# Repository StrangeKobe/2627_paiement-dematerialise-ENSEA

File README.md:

# Plateforme de paiement dématérialisé ENSEA

> Reprise et finalisation d'un système de paiement cashless destiné aux
> associations de l'ENSEA.

**Statut :** reprise du projet / développement en cours\
**Cadre :** projet étudiant ENSEA 2026--2027

------------------------------------------------------------------------

## 1. Présentation

Le projet vise à mettre en place une plateforme de paiement
dématérialisé pour les associations de l'ENSEA.

Le principe est de permettre à un étudiant de disposer d'un
**portefeuille prépayé**, puis d'utiliser ce solde pour effectuer des
achats auprès des associations de l'école.

L'identification prévue repose sur :

-   un **QR code dynamique** ;
-   à terme, la **carte étudiante RFID**.

Le système doit réunir :

-   une application web ;
-   une caisse ;
-   un terminal de paiement portable ;
-   une base de données ;
-   un système de recharge ;
-   des fonctions de suivi des ventes et des soldes.

Le projet est une **reprise d'un travail existant**. Une partie
importante du logiciel et du matériel existe déjà, mais doit être
vérifiée avant d'être considérée comme fonctionnelle.

> **Principe de reprise :** une fonctionnalité annoncée comme réalisée
> doit être testée et classée comme `conforme`, `défaillante` ou
> `non testable`.

------------------------------------------------------------------------

## 2. Objectifs de la V2

L'objectif de la V2 est de disposer d'un ensemble cohérent et
démontrable comprenant :

1.  une application de paiement fonctionnelle ;
2.  une caisse corrigée et testée ;
3.  un terminal de paiement corrigé et testé ;
4.  une identification par QR code et, si possible dans le périmètre
    retenu, par RFID ;
5.  une recharge en ligne réellement intégrée ;
6.  une gestion fiable des soldes et des transactions ;
7.  une documentation permettant la reprise du projet.

Le planning de travail proposé dans le précadrage est de **10
semaines**, à confirmer avec les encadrants.

------------------------------------------------------------------------

## 3. État actuel

### 3.1 Logiciel

  Élément                 État actuel
  ----------------------- -----------------------------------------------------
  Backend                 Django
  Base de développement   SQLite
  Interface               Templates Django + Bootstrap
  QR code                 QR dynamique / caméra du navigateur
  Paiement en ligne       HelloAsso prévu, intégration réelle à terminer
  RFID                    Champ `uid_rfid` présent, lecture réelle à intégrer
  Exports                 Excel avec `openpyxl`
  Emails                  Reçus et codes selon la configuration

### 3.2 Fonctionnalités déclarées comme réalisées

Le projet initial déclare notamment :

-   portefeuille prépayé par étudiant ;
-   débit/crédit atomique ;
-   paiement par QR code dynamique ;
-   vente catalogue ;
-   vente à montant libre ;
-   gestion du catalogue et des stocks ;
-   adhésions ;
-   recharge en espèces ;
-   rôles et droits par pôle ;
-   codes de sécurité ;
-   espace administrateur école ;
-   exports Excel ;
-   reçus par email ;
-   anonymisation après suppression de compte.

**Ces fonctionnalités doivent être vérifiées pendant la phase de
diagnostic.**

### 3.3 Fonctionnalités restantes identifiées

-   intégration réelle de HelloAsso ;
-   lecture RFID ;
-   blocage réversible d'un compte ou d'un QR compromis ;
-   tarif adhérent / non-adhérent ;
-   authentification CAS de l'école ;
-   passage à PostgreSQL ;
-   préparation de la mise en production ;
-   finalisation des CGU ;
-   V2 des PCB ;
-   éventuellement tableau de bord statistique et notifications.

Le périmètre définitif sera validé après le diagnostic.

------------------------------------------------------------------------

## 4. Architecture générale

``` text
                    +--------------------+
                    |      Étudiant      |
                    | QR / carte RFID    |
                    +---------+----------+
                              |
                              v
                    +--------------------+
                    | Application Django |
                    +---------+----------+
                              |
             +----------------+----------------+
             |                |                |
             v                v                v
       +-----------+    +-----------+    +-------------+
       |   Caisse  |    |  Terminal |    |   Recharge  |
       | Raspberry |    |  portable |    |   en ligne  |
       +-----------+    +-----------+    +-------------+
                              |
                              v
                    +--------------------+
                    |   Base de données  |
                    | comptes / soldes / |
                    | ventes / adhésions |
                    +--------------------+
```

------------------------------------------------------------------------

## 5. Fonctionnement cible d'un paiement

``` text
1. L'étudiant présente son QR code ou sa carte
                ↓
2. Le vendeur identifie l'étudiant
                ↓
3. L'application vérifie les droits et le solde
                ↓
4. Le paiement est accepté ou refusé
                ↓
5. Le solde étudiant est débité
                ↓
6. La recette du pôle est enregistrée
                ↓
7. La transaction est conservée dans l'historique
```

Les mécanismes exacts doivent être confirmés par les tests de reprise.

------------------------------------------------------------------------

## 6. Rôles

Le modèle applicatif repose sur des affectations associant un
utilisateur, un pôle, un rôle et éventuellement des droits
supplémentaires.

  -----------------------------------------------------------------------
  Rôle                    Portée                  Fonction principale
  ----------------------- ----------------------- -----------------------
  **Admin école**         Globale                 Comptes, rôles, codes
                                                  de sécurité, recettes
                                                  agrégées

  **Admin ADE**           Globale                 Gestion des pôles et
                                                  opérations ADE

  **Admin de pôle**       Un pôle                 Catalogue, événements,
                                                  équipe, adhésions,
                                                  exports

  **Vendeur**             Un pôle                 Encaissement et ventes
  -----------------------------------------------------------------------

------------------------------------------------------------------------

## 7. Matériel

Le projet comprend deux équipements électroniques.

### 7.1 Caisse

Éléments principaux identifiés :

-   Raspberry Pi 5 ;
-   alimentation ;
-   conversion 12 V → 5 V ;
-   commande du tiroir-caisse ;
-   périphériques d'encaissement.

Le PCB V1 existe mais présente des défauts identifiés dans la
documentation matérielle.

**Travail V2 :**

-   audit du schéma ;
-   vérification des empreintes ;
-   correction des composants de puissance ;
-   vérification de l'alimentation ;
-   vérification du routage ;
-   génération d'une BOM à jour ;
-   fabrication ;
-   tests électriques ;
-   tests fonctionnels.

### 7.2 Terminal portable

Éléments principaux identifiés :

-   Raspberry Pi Zero 2 W ;
-   HAT UPS Geekworm X306 ;
-   batterie 18650 ;
-   RC522 ;
-   écran OLED SSD1327 ;
-   périphériques d'identification et de signalisation.

Le PCB V1 doit également être vérifié et corrigé avant une nouvelle
fabrication.

> Le lecteur QR actuellement disponible est identifié comme **à
> revoir**, notamment concernant son interface. Ne pas commander une
> nouvelle série de cartes ou de composants avant validation.

------------------------------------------------------------------------

## 8. Structure du dépôt

``` text
2026_Stage_Caisse_Ensea/
│
├── README.md
│
├── Documents/
│   ├── conformite_reglementaire/
│   ├── Systèmes de paiment/
│   └── Réunion/
│
├── Hardware/
│   ├── README.md
│   ├── PROBLEMES_MATERIEL.md
│   ├── PCB_Caisse_Enregistreuse/
│   └── PCB_Caisse_Dématérialisée/
│
├── Software/
│   ├── README.md
│   ├── Raspberry/
│   ├── Diagramme_BDD/
│   ├── Tutoriel_Application_Cashless_ENSEA/
│   ├── First_Test_Appli_Django/
│   └── Ancienne_réflexion/
│
└── Images/
```

### Documents importants

  Besoin                           Document / dossier
  -------------------------------- ---------------------------------------
  Comprendre l'application         `Software/README.md`
  Comprendre la base et les flux   `Software/Diagramme_BDD/`
  Installer les Raspberry Pi       `Software/Raspberry/`
  Reprendre les PCB                `Hardware/README.md`
  Problèmes matériels connus       `Hardware/PROBLEMES_MATERIEL.md`
  Réglementation                   `Documents/conformite_reglementaire/`
  Benchmark / prestataires         `Documents/Systèmes de paiment/`
  Historique                       `Documents/Réunion/`

Les dossiers `Software/First_Test_Appli_Django/` et
`Software/Ancienne_réflexion/` sont historiques et ne décrivent pas
nécessairement l'architecture actuelle.

------------------------------------------------------------------------

## 9. Plan de reprise
## Planning du projet

Le projet a débuté le **23 septembre 2026** et la livraison est prévue
début **mars 2027**.

Le planning est structuré selon les lots du WBS présentés dans le document
de précadrage.

```mermaid
gantt
    title Projet Paiement dématérialisé ENSEA V2
    dateFormat YYYY-MM-DD
    axisFormat %d/%m

    section W1 — Cadrage

    Cadrage du projet                 :w1_1, 2026-09-23, 10d
    Définition du périmètre V2       :w1_2, 2026-09-29, 12d
    Objectifs / contraintes / risques :w1_3, 2026-10-02, 10d
    Document de précadrage            :w1_4, 2026-10-05, 12d
    Jalon — Cadrage terminé          :milestone, w1_end, 2026-10-16, 0d

    section W2 — Diagnostic

    Reprise du dépôt                 :w2_1, 2026-09-23, 15d
    Audit logiciel                   :w2_2, 2026-10-05, 15d
    Audit matériel                   :w2_3, 2026-10-05, 20d
    Inventaire des anomalies         :w2_4, 2026-10-12, 10d
    Diagnostic final                 :w2_5, 2026-10-12, 10d
    Jalon — Diagnostic terminé       :milestone, w2_end, 2026-10-23, 0d

    section W3 — Correction du socle

    Corrections prioritaires         :w3_1, 2026-10-19, 15d
    Tests de non-régression          :w3_2, 2026-10-26, 15d
    Sécurisation des transactions    :w3_3, 2026-10-26, 20d
    Validation du socle              :w3_4, 2026-11-09, 5d
    Jalon — Socle fiabilisé          :milestone, w3_end, 2026-11-13, 0d

    section W4 — Compléter le logiciel

    HelloAsso                        :w4_1, 2026-11-09, 25d
    RFID                             :w4_2, 2026-11-16, 20d
    Blocage / déblocage              :w4_3, 2026-11-23, 15d
    Gestion des droits               :w4_4, 2026-11-23, 20d
    Authentification CAS             :w4_5, 2026-12-01, 30d
    Tests des fonctionnalités        :w4_6, 2027-01-04, 10d

    section W5 — Finaliser le matériel

    Audit PCB V1                     :w5_1, 2026-10-05, 20d
    Vérification schémas / empreintes:w5_2, 2026-10-12, 20d
    Correction PCB V2                :w5_3, 2026-10-26, 20d
    Validation BOM                   :w5_4, 2026-11-09, 10d
    Commande composants              :w5_5, 2026-11-16, 7d
    Fabrication PCB                  :w5_6, 2026-11-23, 20d
    Assemblage                       :w5_7, 2026-12-07, 15d
    Tests électriques                :w5_8, 2026-12-14, 15d
    Tests périphériques              :w5_9, 2027-01-04, 10d
    Jalon — Hardware validé          :milestone, w5_end, 2027-01-15, 0d

    section W6 — Préparer l'exploitation

    Migration vers PostgreSQL        :w6_1, 2026-12-14, 20d
    Préparation serveur              :w6_2, 2027-01-04, 20d
    HTTPS / sécurité                 :w6_3, 2027-01-04, 20d
    Sauvegarde / restauration        :w6_4, 2027-01-11, 15d
    Tests d'exploitation             :w6_5, 2027-01-18, 10d

    section W7 — Intégration et validation

    Intégration de la caisse         :w7_1, 2027-01-11, 10d
    Intégration du terminal          :w7_2, 2027-01-11, 10d
    Communication matériel / serveur:w7_3, 2027-01-18, 10d
    Tests parcours de paiement       :w7_4, 2027-01-25, 15d
    Tests recharge                   :w7_5, 2027-01-25, 15d
    Tests RFID / QR                  :w7_6, 2027-02-01, 10d
    Tests de sécurité                :w7_7, 2027-02-08, 10d
    Tests de non-régression          :w7_8, 2027-02-15, 10d
    Corrections finales              :w7_9, 2027-02-15, 10d
    Jalon — V2 validée               :milestone, w7_end, 2027-02-26, 0d

    section W8 — Documentation et livraison

    Documentation technique          :w8_1, 2027-01-25, 25d
    Documentation hardware           :w8_2, 2027-02-01, 20d
    Documentation utilisateur        :w8_3, 2027-02-08, 15d
    Nettoyage du dépôt GitHub        :w8_4, 2027-02-22, 5d
    Préparation démonstration        :w8_5, 2027-02-22, 10d
    Livraison finale                 :milestone, w8_end, 2027-03-05, 0d
```

### Phase 1 --- Diagnostic

-   installer et lancer le logiciel ;
-   vérifier les dépendances ;
-   parcourir les fonctionnalités ;
-   inventorier le matériel ;
-   inspecter les deux PCB ;
-   tester les fonctions annoncées comme réalisées ;
-   établir le registre des anomalies.

**Livrable :** rapport de diagnostic.

### Phase 2 --- Fiabilisation

-   corriger les anomalies bloquantes ;
-   refaire les tests ;
-   vérifier qu'aucune fonction essentielle n'a été dégradée.

### Phase 3 --- Finalisation logiciel

Priorités identifiées :

-   recharge en ligne ;
-   RFID ;
-   blocage réversible ;
-   droits et limites ;
-   authentification CAS ;
-   PostgreSQL ;
-   préparation de l'exploitation.

### Phase 4 --- Finalisation matériel

-   corriger les PCB ;
-   valider les empreintes ;
-   finaliser la nomenclature ;
-   commander les composants ;
-   fabriquer les cartes ;
-   effectuer les tests d'alimentation ;
-   tester les périphériques ;
-   tester la communication avec l'application.

### Phase 5 --- Intégration

``` text
Application
     |
     +---- Caisse
     |
     +---- Terminal
              |
              +---- Identification étudiant
```

Effectuer ensuite les tests de bout en bout.

### Phase 6 --- Documentation

Livrer :

-   code ;
-   schémas ;
-   PCB ;
-   nomenclatures ;
-   procédures d'installation ;
-   procédures de test ;
-   documentation utilisateur ;
-   registre des anomalies ;
-   résultats de validation.

------------------------------------------------------------------------

## 10. Critères de validation proposés

Les critères suivants sont issus du précadrage et devront être confirmés
au lancement.

### Diagnostic

-   100 % des fonctionnalités annoncées sont testées ;
-   chaque élément est classé `conforme`, `défaillant` ou
    `non testable`.

### Matériel

-   caisse alimentée et démarrée correctement ;
-   terminal alimenté et démarré correctement ;
-   lecteurs et affichages fonctionnels ;
-   20 lectures successives d'une carte autorisée ;
-   refus d'une carte inconnue.

### Paiement

-   paiements acceptés correctement ;
-   paiements refusés correctement ;
-   absence de double débit ;
-   solde cohérent ;
-   stock cohérent.

### Livraison

-   20 achats de test consécutifs sans erreur de solde ou de stock ;
-   aucun défaut bloquant restant ;
-   documentation remise ;
-   démonstration réalisable par une personne extérieure au binôme à
    partir du guide.

> Ces critères sont des objectifs de validation et non la preuve que les
> fonctions sont déjà conformes.

------------------------------------------------------------------------

## 11. Planning indicatif

Le planning proposé dans le précadrage est de 10 semaines.

  Période   Étape           Objectif
  --------- --------------- --------------------------------------
  S1--S2    Diagnostic      Connaître l'état réel
  S3--S4    Fiabilisation   Corriger le socle
  S2--S7    Logiciel        Finaliser les fonctions prioritaires
  S2--S8    Matériel        Corriger et fabriquer les V2
  S3--S9    Exploitation    Hébergement, sécurité, sauvegarde
  S6--S10   Intégration     Tester l'ensemble
  S8--S10   Documentation   Préparer la livraison

### Jalons

-   **J0 --- S1 :** lancement ;
-   **J1 --- S2 :** diagnostic ;
-   **J2 --- S4 :** socle fiabilisé ;
-   **J3 --- S8 :** ensemble intégré ;
-   **J4 --- S10 :** réception pédagogique.

------------------------------------------------------------------------

## 12. Risques principaux

  ------------------------------------------------------------------------
  Risque                                      Niveau Action
  --------------------- ---------------------------- ---------------------
  État réel différent                          Élevé Diagnostic initial
  de la documentation                                complet

  Défauts PCB /                                Élevé Audit matériel avant
  composants                                         commande

  Retard                                       Élevé Identifier tôt les
  d'approvisionnement                                composants critiques

  Intégration HelloAsso                  Moyen/élevé Obtenir les accès et
                                                     tester les scénarios

  Erreur de solde /                            Élevé Tests transactionnels
  double paiement                                    et cas limites

  Accès non autorisé                           Élevé Tester rôles,
                                                     blocages et
                                                     authentification

  Perte de données                             Élevé Sauvegarde et
                                                     restauration

  Périmètre trop                               Élevé Prioriser les
  important                                          fonctions
                                                     essentielles
  ------------------------------------------------------------------------

------------------------------------------------------------------------

## 13. Décisions encore à prendre

Avant de considérer la V2 comme figée :

-   date officielle de livraison ;
-   répartition nominative des responsabilités ;
-   budget et responsable des commandes ;
-   utilisateurs pilotes ;
-   périmètre exact de la V2 ;
-   lecteur QR retenu ;
-   stratégie RFID ;
-   environnement d'hébergement ;
-   accès HelloAsso ;
-   intégration CAS ;
-   base PostgreSQL ;
-   règles de gestion et de remboursement des soldes ;
-   conditions d'utilisation avec de l'argent réel.

------------------------------------------------------------------------

## 14. Règles importantes pour la reprise

1.  **Ne pas considérer une fonctionnalité comme acquise sans test.**
2.  **Ne pas modifier le matériel avant d'avoir documenté l'état V1.**
3.  **Ne pas commander les PCB V2 avant validation des schémas,
    empreintes et BOM.**
4.  **Ne jamais utiliser de `float` pour les montants monétaires :
    utiliser `Decimal`.**
5.  **Les transactions de solde doivent rester atomiques et protégées
    contre les accès concurrents.**
6.  **Ne pas supprimer physiquement les comptes si cela détruit
    l'historique nécessaire ; suivre la politique d'anonymisation
    prévue.**
7.  **Les documents historiques ne décrivent pas nécessairement
    l'architecture actuelle.**
8.  **L'utilisation avec de l'argent réel est une décision distincte de
    la démonstration technique.**

------------------------------------------------------------------------

## 15. État du document

  Élément                Valeur
  ---------------------- ---------------------------------
  Version                0.1
  Statut                 Brouillon de reprise
  Projet                 Paiement dématérialisé ENSEA V2
  Source principale      README initial du projet
  Complément             Document de précadrage V2
  Dernière mise à jour   À renseigner

------------------------------------------------------------------------

## Licence

Projet interne ENSEA --- usage restreint aux associations et acteurs
autorisés de l'école.

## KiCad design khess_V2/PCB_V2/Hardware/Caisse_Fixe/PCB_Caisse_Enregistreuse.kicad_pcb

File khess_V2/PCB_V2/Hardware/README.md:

# Hardware — projets corrigés V2

Les deux projets sont indépendants et possèdent leurs propres bibliothèques locales. Conserver tous les fichiers de chaque dossier ensemble, puis ouvrir le `.kicad_pro` avec KiCad 9. Le schéma de la caisse comporte une feuille hiérarchique `Power_supply.kicad_sch` : conserver ce nom et son emplacement.

## Alimentation et commandes

| Carte / signal | GPIO BCM | Broche physique du Pi | Remarque |
|---|---:|---:|---|
| Caisse : Ouv_Tiroir | 18 | 12 | Q3, actif HIGH, impulsion limitée |
| Caisse : Buzzer_PWM | 23 | 16 | Q1, actif HIGH ; nom de net historique |
| Terminal : Buzzer_PWM | **19** | **35** | Q1, actif HIGH ; pas GPIO18 |
| Terminal : RFID_NSS | **8 / CE0** | **24** | Pas CE1 / broche26 |
| Terminal : OLED_CS | 7 / CE1 | 26 | Brochage existant conservé |
| Terminal : sortie UART du Pi | 14 / TXD0 | 8 | Vers l'entrée RX du lecteur |
| Terminal : entrée UART du Pi | 15 / RXD0 | 10 | Depuis la sortie TX du lecteur |

Ces affectations proviennent des schémas et netlists livrés. Le logiciel n'est pas modifié dans cette archive : vérifier sa configuration GPIO avec ce tableau et initialiser les commandes MOSFET à LOW au démarrage.

### Caisse fixe

- J2 : entrée jack 12 V ; J3 : interrupteur externe entre +12V_RAW (broche1) et +12V_SW (broche2).
- J1 : tiroir, broche1 = +12V_SW, broche2 = drain Q3 / anode D6.
- D6 : cathode sur +12V_SW, anode sur le drain. Contrôler la soudure et le courant réel du solénoïde.
- D8 protège la grille de Q1, **au dessous du PCB** ; D9 protège Q3, au dessus.
- La source d'alimentation 12 V / 2 A mentionnée dans la documentation initiale limite la puissance disponible ; qualifier le fonctionnement du Pi 5 sous sa charge réelle.

### Terminal mobile

J1, connecteur QR à 4 broches :

| Broche | Signal | Sens |
|---:|---|---|
| 1 | +5 V | Alimentation du lecteur, vérifier sa consommation |
| 2 | GND | Masse commune |
| 3 | Lecteur_QR_RX | Pi TX GPIO14 → lecteur RX |
| 4 | Lecteur_QR_TX | Lecteur TX → Pi RX GPIO15 |

Les signaux des broches 3/4 doivent être compatibles **logique 3,3 V**. L'alimentation 5 V de la broche1 ne signifie pas que les GPIO tolèrent 5 V. Ce connecteur n'est ni USB ni RS232. Un lecteur USB se branche sur le port USB du Pi avec la connectique appropriée.

L'alimentation du terminal reste celle du montage Pi Zero 2 W / HAT X306. Cette révision ne modifie pas le chargeur de batterie externe.

### Buzzer des deux cartes

La V2 retient le **CMI-1295-0585T**, buzzer magnétique actif 5 V, polarisé, boîtier 12 × 9,5 mm et entraxe 7,6 mm. Un niveau HIGH sur la commande MOSFET l'alimente ; LOW l'arrête. Le nom historique `Buzzer_PWM` est conservé pour éviter une modification inutile de l'interface logicielle, mais ne prescrit pas un PWM audio.

Le **PS1720P02 passif** cité dans le retour d'expérience V1 est un autre composant : ne pas le monter comme équivalent direct. Voir les limites et les essais restants dans `../MODIFICATIONS.md`.

## Bibliothèques et fabrication

Les empreintes locales sont des copies de la géométrie embarquée dans chaque carte ; les noms correspondent aux références (Q1, D8, etc.). Les symboles locaux dérivent des symboles embarqués d'origine et des bibliothèques KiCad. Leur présence empêche une mise à jour depuis un ancien symbole NMOS incorrect.

Les cartes conservent leurs **quatre couches cuivre**, leur contour et leurs découpes. Les Gerber à utiliser pour examiner le prototype sont dans `../Fabrication_prototype/`. Ne pas mélanger ces exports avec ceux de la V1. Les modèles 3D standard restent référencés par la variable KiCad `KICAD9_3DMODEL_DIR` et sont facultatifs pour éditer les schémas et PCB.

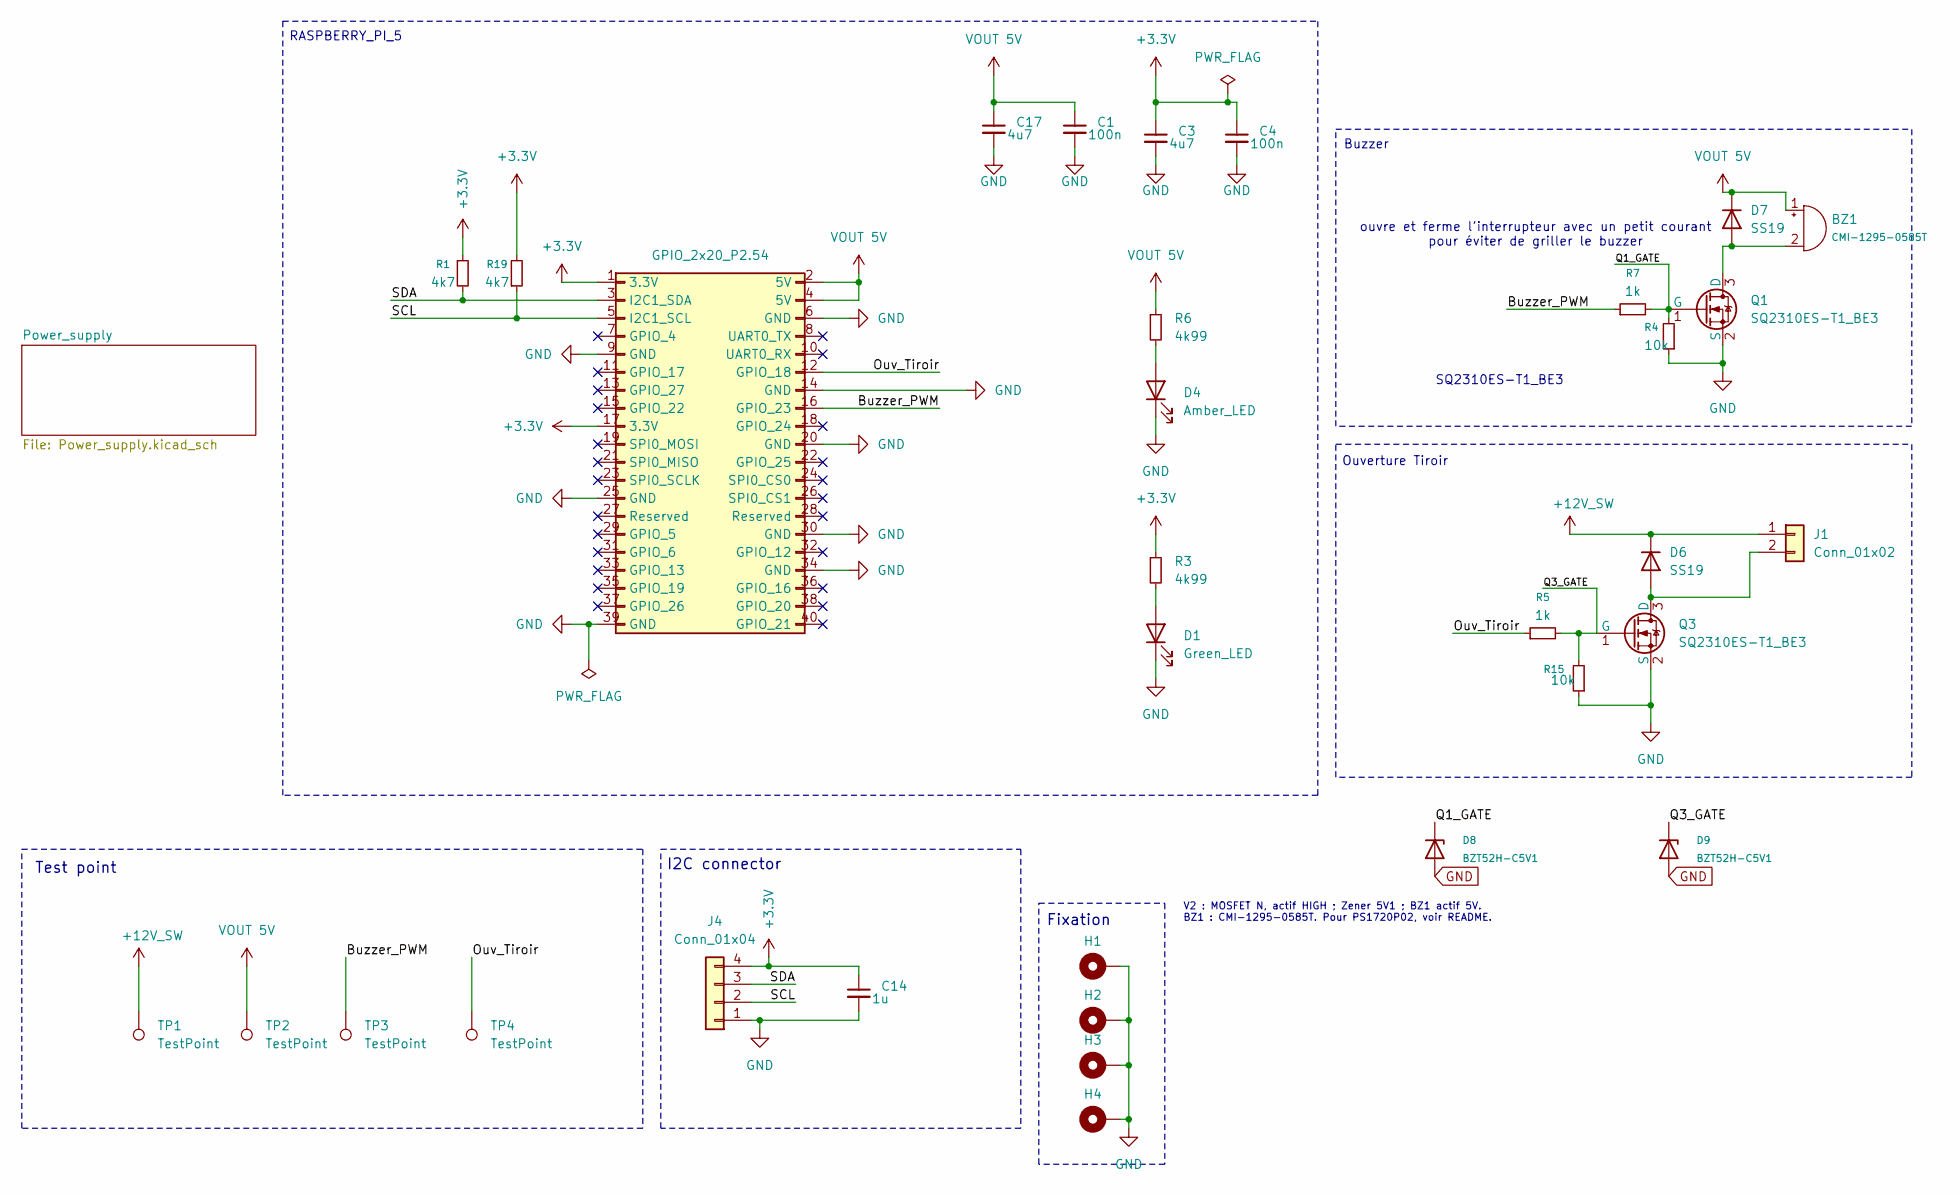
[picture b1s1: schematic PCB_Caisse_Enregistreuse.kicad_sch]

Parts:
BZ1: CMI-1295-0585T; BZ1; MPN CMI-1295-0585T
C1: 100n; C1; MPN KAM15AR71C104KM
C3: 4u7; C3; MPN 885012106025
C4: 100n; C4; MPN KAM15AR71C104KM
C14: 1u; C14; MPN 885012206002
C17: 4u7; C17; MPN 885012106025
D1: Green_LED; D1; MPN 150060GS55040
D4: Amber_LED; D4; MPN 150060AS55040
D6: SS19; D6; MPN SS19
D7: SS19; D7; MPN SS19
D8: BZT52H-C5V1; D8; MPN BZT52H-C5V1,115
D9: BZT52H-C5V1; D9; MPN BZT52H-C5V1,115
H1: MountingHole_Pad; H1; MPN N/A - element cuivre/mecanique du PCB
H2: MountingHole_Pad; H2; MPN N/A - element cuivre/mecanique du PCB
H3: MountingHole_Pad; H3; MPN N/A - element cuivre/mecanique du PCB
H4: MountingHole_Pad; H4; MPN N/A - element cuivre/mecanique du PCB
J1: Conn_01x02; J1; MPN B2B-XH-A(LF)(SN)
J4: Conn_01x04; J4; MPN B4B-XH-A(LF)(SN)
Q1: SQ2310ES-T1_BE3; Q1; MPN SQ2310ES-T1_BE3
Q3: SQ2310ES-T1_BE3; Q3; MPN SQ2310ES-T1_BE3
R1: 4k7; R1; MPN RC0603FR-074K7L
R3: 4k99; R3; MPN RC0603FR-074K99L
R4: 10k; R4; MPN RC0603FR-0710KL
R5: 1k; R5; MPN RC0603FR-071KL
R6: 4k99; R6; MPN RC0603FR-074K99L
R7: 1k; R7; MPN RC0603FR-071KL
R15: 10k; R15; MPN RC0603FR-0710KL
R19: 4k7; R19; MPN RC0603FR-074K7L
TP1: TestPoint; TP1; MPN N/A - element cuivre/mecanique du PCB
TP2: TestPoint; TP2; MPN N/A - element cuivre/mecanique du PCB
TP3: TestPoint; TP3; MPN N/A - element cuivre/mecanique du PCB
TP4: TestPoint; TP4; MPN N/A - element cuivre/mecanique du PCB
U1: GPIO_2x20_P2.54; U1; MPN 61304021121

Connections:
+3.3V: C3.1, C4.1, C14.1, J4.4, R1.1, R3.1, R19.2, U1.1 (3.3V), U1.17 (3.3V)
+12V_SW: D6.1 (K), J1.1, TP1.1; also elsewhere on the board
/Buzzer_PWM: R7.1, TP3.1, U1.16 (GPIO_23)
/Ouv_Tiroir: R5.1, TP4.1, U1.12 (GPIO_18)
/Q1_GATE: D8.1 (K), Q1.1 (G), R4.2, R7.2
/Q3_GATE: D9.1 (K), Q3.1 (G), R5.2, R15.2
/SCL: J4.2, R19.1, U1.5 (I2C1_SCL)
/SDA: J4.3, R1.2, U1.3 (I2C1_SDA)
GND: C1.2, C3.2, C4.2, C14.2, C17.2, D1.1 (K), D4.1 (K), D8.2 (A), D9.2 (A), H1.1, H2.1, H3.1, H4.1, J4.1, Q1.2 (S), Q3.2 (S), R4.1, R15.1, U1.6 (GND), U1.9 (GND), U1.14 (GND), U1.20 (GND), U1.25 (GND), U1.30 (GND), U1.34 (GND), U1.39 (GND); also elsewhere on the board
unnamed: BZ1.2 (-), D7.2 (A), Q1.3 (D)
unnamed: D1.2 (A), R3.2
unnamed: D4.2 (A), R6.2
unnamed: D6.2 (A), J1.2, Q3.3 (D)
VOUT 5V: BZ1.1 (+), C1.1, C17.1, D7.1 (K), R6.1, TP2.1, U1.2 (5V), U1.4 (5V); also elsewhere on the board

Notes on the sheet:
Fixation
RASPBERRY_PI_5
V2 : MOSFET N, actif HIGH ; Zener 5V1 ; BZ1 actif 5V. BZ1 : CMI-1295-0585T. Pour PS1720P02, voir README.
ouvre et ferme l'interrupteur avec un petit courant pour éviter de griller le buzzer
Ouverture Tiroir
SQ2310ES-T1_BE3
I2C connector
Test point
Buzzer

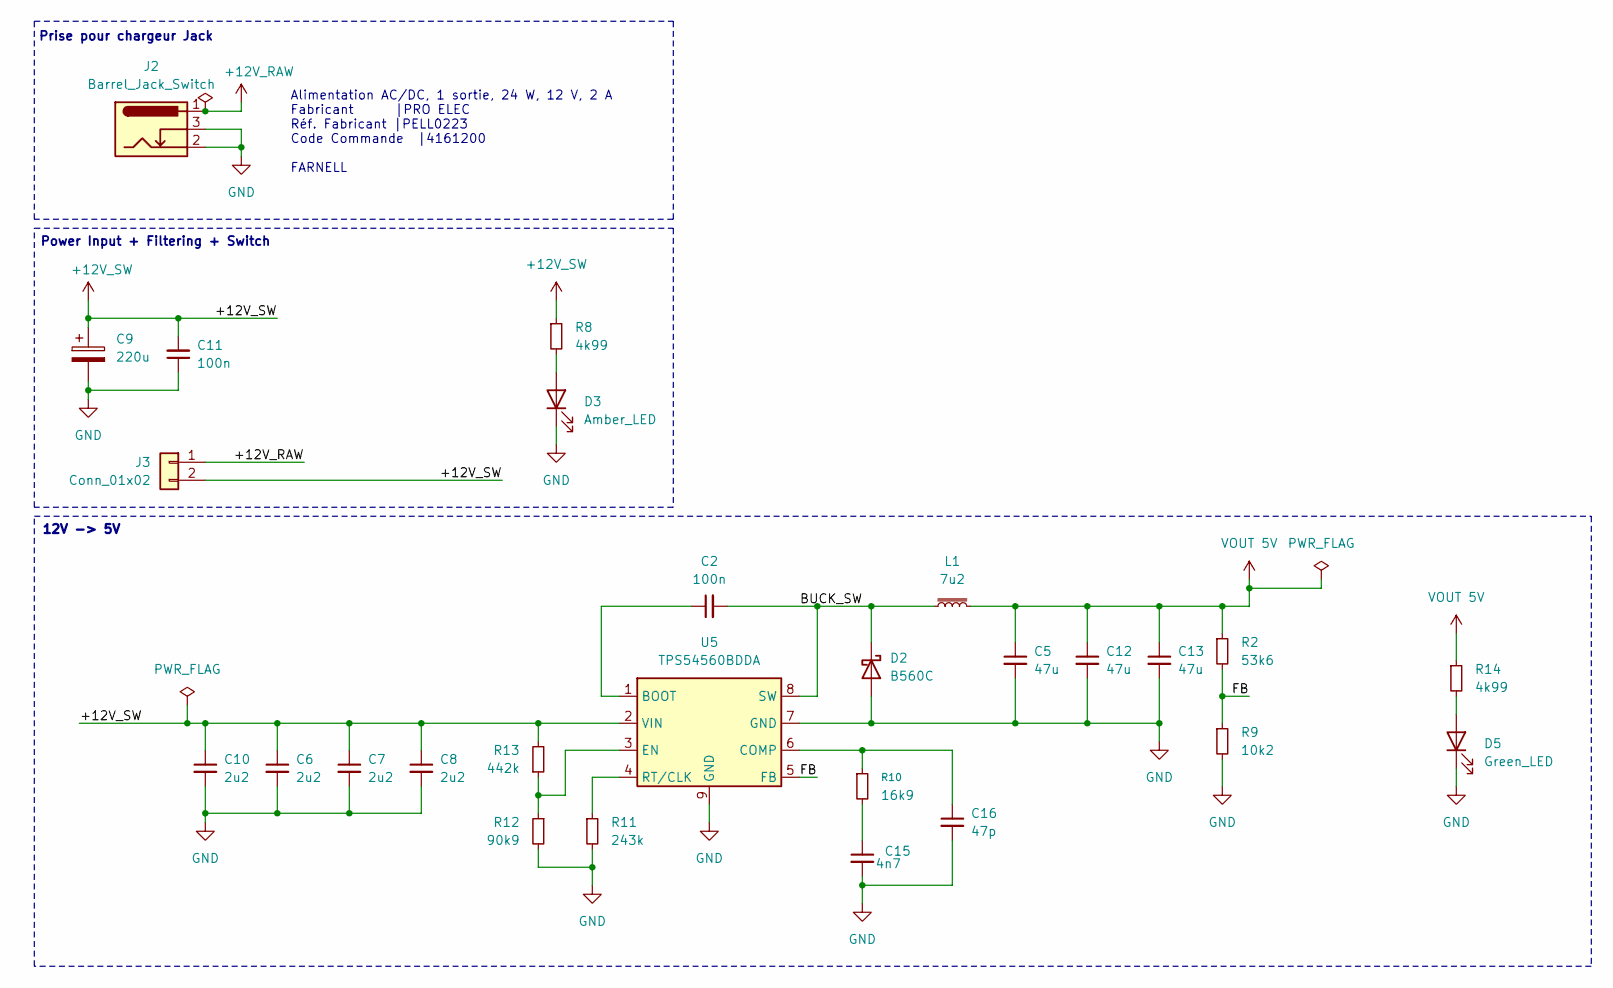
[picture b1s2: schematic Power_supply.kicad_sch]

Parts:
C2: 100n; C2; MPN KAM15AR71C104KM
C5: 47u; C5; MPN 885012109011
C6: 2u2; C6; MPN 885012106029
C7: 2u2; C7; MPN 885012106029
C8: 2u2; C8; MPN 885012106029
C9: 220u; C9; MPN 865060657012
C10: 2u2; C10; MPN 885012106029
C11: 100n; C11; MPN KAM15AR71C104KM
C12: 47u; C12; MPN 885012109011
C13: 47u; C13; MPN 885012109011
C15: 4n7; C15; MPN CC0805JRNPO9BN472
C16: 47p; C16; MPN 06035U470GAT2A
D2: B560C; D2; MPN B560C-13-F
D3: Amber_LED; D3; MPN 150060AS55040
D5: Green_LED; D5; MPN 150060GS55040
J2: Barrel_Jack_Switch; J2; MPN FC681465S
J3: Conn_01x02; J3; MPN B2B-XH-A(LF)(SN)
L1: 7u2; L1; MPN PM5433.722NLT
R2: 53k6; R2; MPN AC0603FR-1353K6L
R8: 4k99; R8; MPN RC0603FR-074K99L
R9: 10k2; R9; MPN AC0603FR-1310K2L
R10: 16k9; R10; MPN AA0603FR-0716K9L
R11: 243k; R11; MPN RT0603DRE07243KL
R12: 90k9; R12; MPN RC0603FR-0790K9L
R13: 442k; R13; MPN ERJ-S03F4423V
R14: 4k99; R14; MPN RC0603FR-074K99L
U5: TPS54560BDDA; U5; MPN TPS54560BDDA

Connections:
+12V_RAW: J2.1, J3.1
+12V_SW: C6.1, C7.1, C8.1, C9.1, C10.1, C11.2, J3.2, R8.1, R13.2, U5.2 (VIN); also elsewhere on the board
/Power_supply/BUCK_SW: C2.2, D2.1 (K), L1.1, U5.8 (SW)
/Power_supply/FB: R2.2, R9.1, U5.5 (FB)
GND: C5.2, C6.2, C7.2, C8.2, C9.2, C10.2, C11.1, C12.2, C13.2, C15.2, C16.2, D2.2 (A), D3.1 (K), D5.1 (K), J2.2, J2.3, R9.2, R11.2, R12.2, U5.7 (GND), U5.9 (GND); also elsewhere on the board
unnamed: C15.1, R10.2
unnamed: D3.2 (A), R8.2
unnamed: D5.2 (A), R14.2
unnamed: C2.1, U5.1 (BOOT)
unnamed: C16.1, R10.1, U5.6 (COMP)
unnamed: R12.1, R13.1, U5.3 (EN)
unnamed: R11.1, U5.4 (RT/CLK)
VOUT 5V: C5.1, C12.1, C13.1, L1.2, R2.1, R14.1; also elsewhere on the board

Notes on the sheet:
Prise pour chargeur Jack
12V -> 5V
Alimentation AC/DC, 1 sortie, 24 W, 12 V, 2 A Fabricant |PRO ELEC Réf. Fabricant |PELL0223 Code Commande |4161200 FARNELL
Power Input + Filtering + Switch

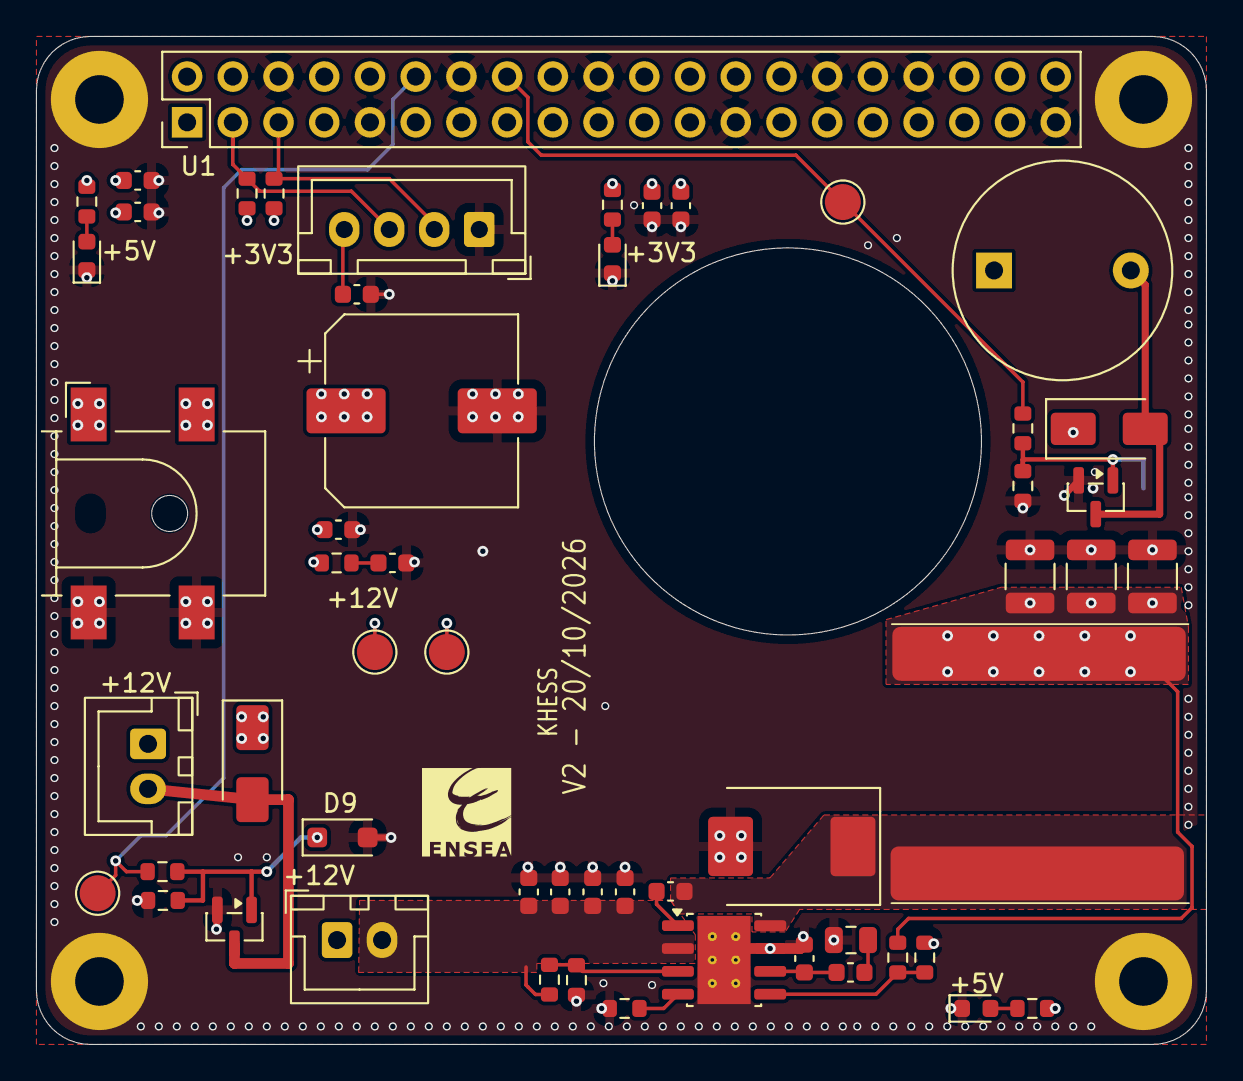
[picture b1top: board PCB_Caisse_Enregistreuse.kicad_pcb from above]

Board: 4 copper layers, 65.0 x 56.0 mm, 60 parts (1 on the bottom side), 24 nets.

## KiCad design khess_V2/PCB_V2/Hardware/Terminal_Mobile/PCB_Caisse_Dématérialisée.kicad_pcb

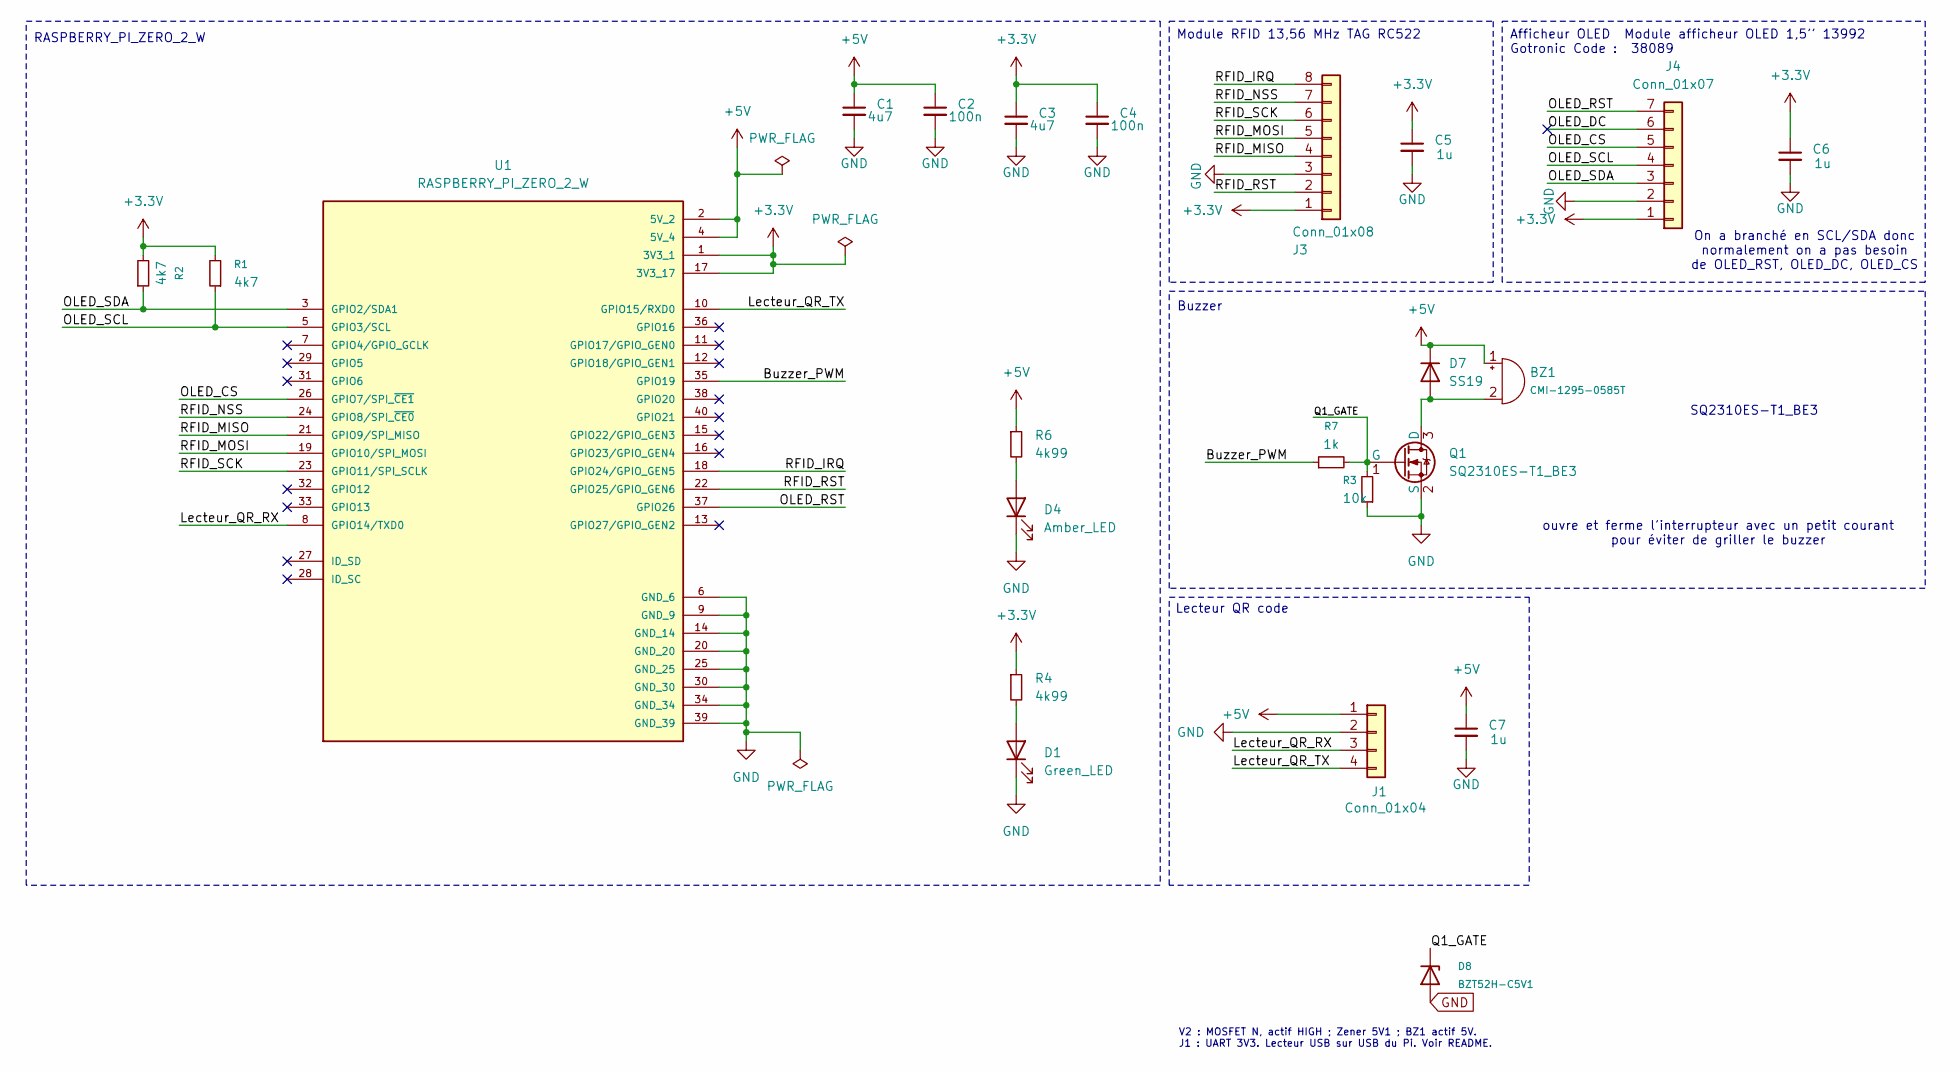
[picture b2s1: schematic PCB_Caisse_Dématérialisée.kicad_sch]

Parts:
BZ1: CMI-1295-0585T; BZ1; MPN CMI-1295-0585T
C1: 4u7; C1; MPN 885012106025
C2: 100n; C2; MPN KAM15AR71C104KM
C3: 4u7; C3; MPN 885012106025
C4: 100n; C4; MPN KAM15AR71C104KM
C5: 1u; C5; MPN 885012206002
C6: 1u; C6; MPN 885012206002
C7: 1u; C7; MPN 885012206002
D1: Green_LED; D1; MPN 150060GS55040
D4: Amber_LED; D4; MPN 150060AS55040
D7: SS19; D7; MPN SS19
D8: BZT52H-C5V1; D8; MPN BZT52H-C5V1,115
J1: Conn_01x04; J1; MPN B4B-PH-K-S(LF)(SN)
J3: Conn_01x08; J3; MPN B8B-PH-K-S(LF)(SN)
J4: Conn_01x07; J4; MPN B7B-PH-K-S(LF)(SN)
Q1: SQ2310ES-T1_BE3; Q1; MPN SQ2310ES-T1_BE3
R1: 4k7; R1; MPN RC0603FR-074K7L
R2: 4k7; R2; MPN RC0603FR-074K7L
R3: 10k; R3; MPN RC0603FR-0710KL
R4: 4k99; R4; MPN RC0603FR-074K99L
R6: 4k99; R6; MPN RC0603FR-074K99L
R7: 1k; R7; MPN RC0603FR-071KL
U1: RASPBERRY_PI_ZERO_2_W; U1; PARTREV April 2024

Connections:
+3.3V: C3.1, C4.1, C5.1, C6.1, J3.1, J4.1, R1.2, R2.2, R4.1, U1.1 (3V3_1), U1.17 (3V3_17)
+5V: BZ1.1 (+), C1.1, C2.1, C7.1, D7.1 (K), J1.1, R6.1, U1.2 (5V_2), U1.4 (5V_4)
/Buzzer_PWM: R7.1, U1.35 (GPIO19)
/Lecteur_QR_RX: J1.3, U1.8 (GPIO14/TXD0)
/Lecteur_QR_TX: J1.4, U1.10 (GPIO15/RXD0)
/OLED_CS: J4.5, U1.26 (GPIO7/SPI_~CE1)
/OLED_DC: J4.6
/OLED_RST: J4.7, U1.37 (GPIO26)
/OLED_SCL: J4.4, R1.1, U1.5 (GPIO3/SCL)
/OLED_SDA: J4.3, R2.1, U1.3 (GPIO2/SDA1)
/Q1_GATE: D8.1 (K), Q1.1 (G), R3.2, R7.2
/RFID_IRQ: J3.8, U1.18 (GPIO24/GPIO_GEN5)
/RFID_MISO: J3.4, U1.21 (GPIO9/SPI_MISO)
/RFID_MOSI: J3.5, U1.19 (GPIO10/SPI_MOSI)
/RFID_NSS: J3.7, U1.24 (GPIO8/SPI_~CE0)
/RFID_RST: J3.2, U1.22 (GPIO25/GPIO_GEN6)
/RFID_SCK: J3.6, U1.23 (GPIO11/SPI_SCLK)
GND: C1.2, C2.2, C3.2, C4.2, C5.2, C6.2, C7.2, D1.1 (K), D4.1 (K), D8.2 (A), J1.2, J3.3, J4.2, Q1.2 (S), R3.1, U1.6 (GND_6), U1.9 (GND_9), U1.14 (GND_14), U1.20 (GND_20), U1.25 (GND_25), U1.30 (GND_30), U1.34 (GND_34), U1.39 (GND_39)
unnamed: BZ1.2 (-), D7.2 (A), Q1.3 (D)
unnamed: D1.2 (A), R4.2
unnamed: D4.2 (A), R6.2

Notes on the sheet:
Lecteur QR code
Module RFID 13,56 MHz TAG RC522
V2 : MOSFET N, actif HIGH ; Zener 5V1 ; BZ1 actif 5V. J1 : UART 3V3. Lecteur USB sur USB du Pi. Voir README.
ouvre et ferme l'interrupteur avec un petit courant pour éviter de griller le buzzer
RASPBERRY_PI_ZERO_2_W
Afficheur OLED Module afficheur OLED 1,5'' 13992 Gotronic Code : 38089
SQ2310ES-T1_BE3
On a branché en SCL/SDA donc normalement on a pas besoin de OLED_RST, OLED_DC, OLED_CS
Buzzer

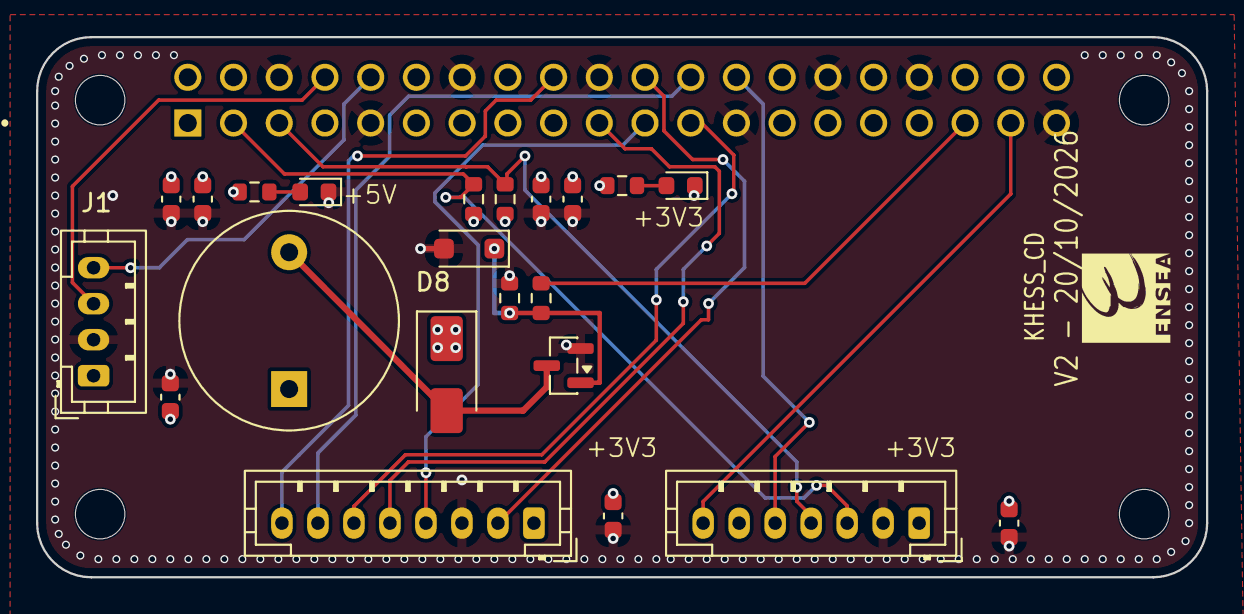
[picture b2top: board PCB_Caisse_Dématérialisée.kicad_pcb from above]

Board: 4 copper layers, 65.0 x 30.0 mm, 25 parts (0 on the bottom side), 20 nets.

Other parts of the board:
EDGE1: EDGE1
EDGE2: EDGE2
